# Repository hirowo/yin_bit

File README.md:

# yin:bit
micro:bit用の拡張モジュールです。micro:bitでフルカラーLED(WS2812B)をコントロールできます。

## 特長
従来からmicro:bitでフルカラーLEDを点灯させるモジュール等はありましたが、  micro:bitから出力される3.3VをフルカラーLEDの電源として使っているものや、電源を単3電池×3本を前提にしている物が多く、安定して光らせられるLEDの数は多くはありませんでした。

本モジュールは、本モジュールについているUSBコネクタから電源供給することで、  micro:bitに給電しつつフルカラーLEDを5V給電することが可能で、micro:bitからフルカラーLEDに給電する際より多くの数のLEDを安定して光らせることができます。

フルカラーLEDの点灯を一時的に抑えたいとき等のために、フルカラーLEDの電源ON/OFFスイッチも実装してあります。

Groveコネクタも実装してありますので、センサの値に応じて好きな色に光らせるといったこともできます。

## 説明動画

## Ver2.0の特徴
光らせたいけどはんだ付けは敷居が高い…という声があり、フルカラーLED部分がGrove互換コネクタが付き、はんだ付け無しでyin:bitを扱えるようになりました。

下記のようなGrove互換コネクタ付きフルカラーLEDを使えます。
 - [Grove - RGB LED (WS2813 Mini)](https://www.seeedstudio.com/Grove-RGB-LED-WS2813-Mini-p-4269.html)
 - [Grove - RGB LED Ring (24-WS2813 Mini)](https://www.seeedstudio.com/Grove-RGB-LED-Ring-24-WS2813-Mini-p-4202.html)
 - [Grove - RGB LED Stick (20-WS2813 Mini)](https://www.seeedstudio.com/Grove-RGB-LED-Stick-20-WS2813-Mini-p-4271.html)
 - [HEX RGB LED Board (SK6812)](https://m5stack.com/products/hex-rgb-led-board-sk6812)
 - [SK6812 RGB LED Flex-strip](https://m5stack.com/collections/m5-unit/products/sk6812-rgb-led-flex-strip)

またいろんなものに組み込むための固定用ネジ穴が追加されました。固定用ネジ穴部を分離するとyin:bitと同サイズになります。

## 使い方

1. yin:bitをmicro:bitにネジで固定します。

2. micro:bitにUSBケーブルを接続します。(プログラムをアプリから無線で書き込む際は不要)

3. micro:bitにプログラムを書き込みます。(プログラムの例は[サンプル](#サンプル)参照)

4. yin:bitにUSBケーブルを差し込み電源と接続します。

5. yin:bitのLED電源スイッチをONします。

## スペック
 - サイズ(v1) : 50.8 × 22.0 × 6.5mm  
 - サイズ(v2) : 68.8 × 24.8 × 8.0mm
 - フルカラーLED用電源電圧(v2だとフルカラーLED用Grove互換コネクタ電源電圧) : 5V
 - フルカラーLED用電源最大電流値 : 2A
 - 入出力用Grove互換コネクタ電源電圧：3.3 V

## ピン
 - フルカラーLEDシリアルピン(v2だとフルカラーLED用Grove互換コネクタ) : P0 
 - 入出力用Grove互換コネクタ : P1/P2

## どこで買える？
 - [スイッチサイエンス](https://www.switch-science.com/catalog/5431/)
 - [スイッチサイエンス(コネクタ実装版)](https://www.switch-science.com/catalog/5821/)
 - [マルツオンライン](https://www.marutsu.co.jp/pc/i/1559574/)
 - [シリコンハウス共立](http://blog.siliconhouse.jp/archives/52170700.html)
 - [Shigezone](https://twitter.com/ShigezoneAkiba/status/1170178701419405312)
 
## サンプル

20個のLEDをついたフルカラーLEDテープを使うことを想定します。

micro:bitでフルカラーLEDを使う場合は「拡張機能」の「NeoPixel」をプロジェクトに追加してください。

### LEDを全て赤色に光らせる

[プログラム例](https://makecode.microbit.org/_FkpHuT0tiH0w)

### LEDを虹色に光らせて流す

[プログラム例](https://makecode.microbit.org/_2kAJboFzL6Ek)

### [Groveのジョイスティック](http://wiki.seeedstudio.com/Grove-Thumb_Joystick/)を使って操作する

[プログラム例](https://makecode.microbit.org/_hW461R9WmUEq)

### 無線を使って遠隔で電飾を操作する

[プログラム例](https://makecode.microbit.org/_WzrJAp9o9Hsq)

### [Groveの超音波距離センサ](http://wiki.seeedstudio.com/Grove-Ultrasonic_Ranger/)を使って操作する

[プログラム例](https://makecode.microbit.org/_3hC7kxe1rCEK)

### おまけ:サーボモーターを動かす

サーボモーターにも使えます。サーボモーターのコードとyin:bitを下記のように繋いでください。

|サーボモーター|yin:bit|
|:-----------:|:------------:|
|茶色|GND|
|赤色|5V|
|黄色|LED_P0|

[プログラム例](https://makecode.microbit.org/_HUk0EjgW45yJ)

## 作品例

### [電飾エプロン](https://twitter.com/GomiHgy/status/1124863205099036674)(by[五味](https://twitter.com/GomiHgy))

### [micro:bitで光るスカート作ったで](https://www.nicovideo.jp/watch/sm35141886)(by[ましぐれ](https://twitter.com/mashigure))

### [サイバリアン電飾](https://twitter.com/i/moments/1194228358986383362)(by[RealizePlus](https://twitter.com/Realize_Plus))

### [光るウエディングドレスと連動する電飾キャンドルサービスを作ってみた](https://youtu.be/PWPQaGGIQgU)(by[静丘](https://twitter.com/Siz_oka))

## 終わりに

yin:bitの改良点がありましたら、ぜひIsuuesに書いてください。
こんな作品作ったよ！という方は [#yinbit](https://twitter.com/search?q=%23yinbit&src=typed_query) を付けてSNSなどで公開してくださると嬉しいです。
よい電飾ライフを！

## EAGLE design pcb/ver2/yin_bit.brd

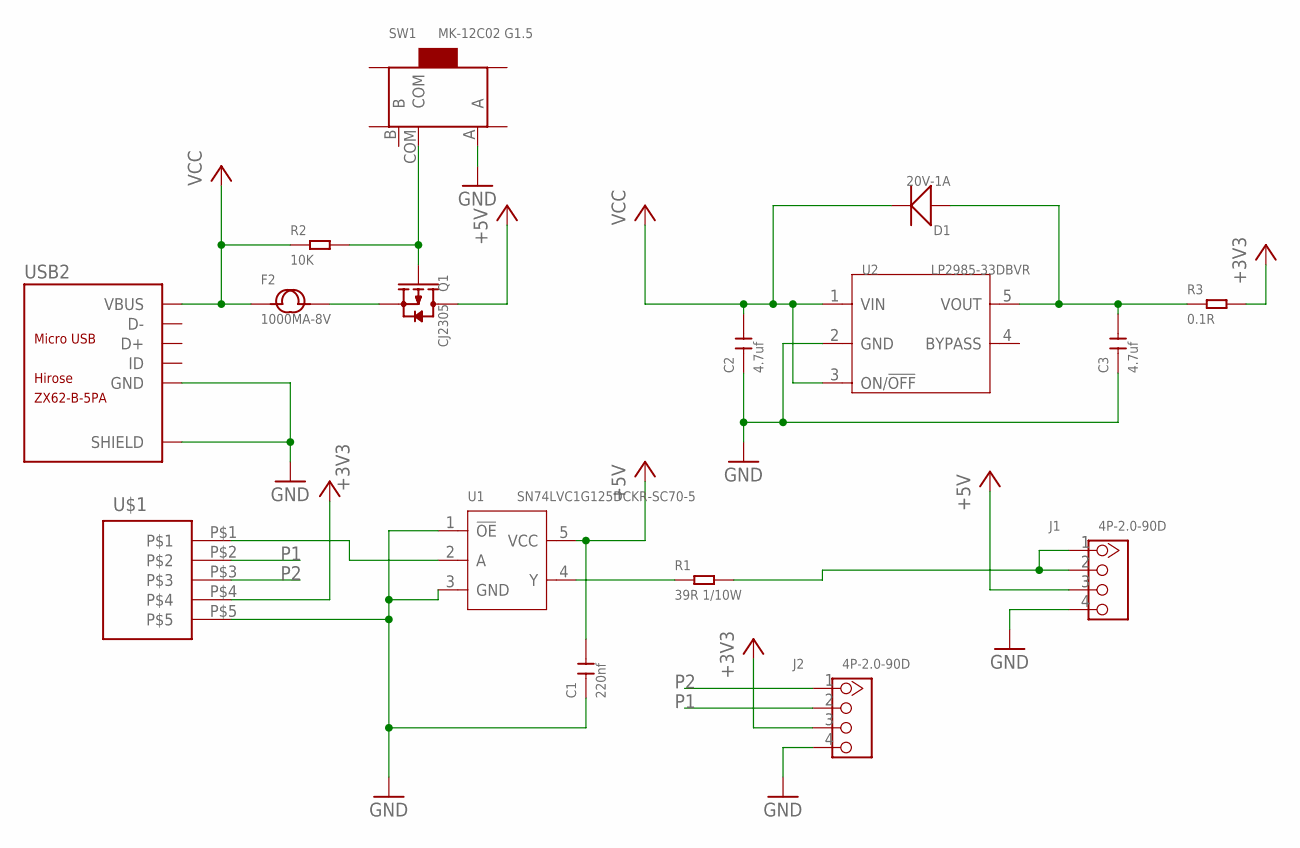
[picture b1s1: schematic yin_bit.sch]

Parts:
C1: 220nf; C0603
C2, C3: 4.7uf; C0603
D1: 20V-1A; SOD-123
F2: 1000MA-8V; F1206
J1, J2: 4P-2.0-90D; HW4-2.0-90D
Q1: CJ2305; SOT-23
R1: 39R 1/10W; R0603
R2: 10K; R0603
R3: 0.1R; R0805
SW1: MK-12C02 G1.5; SW7-SMD-L6.7X2.7X3.2MM
U1: SN74LVC1G125DCKR-SC70-5; SC-70-5
U2: LP2985-33DBVR; SOT-23-5
U$1: MICROBIT-HOLL
USB2: ZX62-B-5PA; MICRO-USB5+6P-SMD-0.65-AB

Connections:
+3V3: J2.3, R3.2, U$1.P$4
+5V: C1.2, J1.3, Q1.3 (D), U1.5 (VCC)
GND: C1.1, C2.1, C3.1, J1.4, J2.4, SW1.A, U1.1 (!OE!), U1.3 (GND), U2.2 (GND), U$1.P$5, USB2.5 (GND), USB2.P1 (SHIELD), USB2.P2 (SHIELD), USB2.P3 (SHIELD), USB2.P4 (SHIELD), USB2.P5 (SHIELD), USB2.P6 (SHIELD)
unnamed: U1.2 (A), U$1.P$1
unnamed: R1.1, U1.4 (Y)
unnamed: J1.1, J1.2, R1.2
unnamed: Q1.1 (G), R2.2, SW1.COM
unnamed: F2.2, Q1.2 (S)
unnamed: C3.2, D1.+, R3.1, U2.5 (VOUT)
P1: J2.2, U$1.P$2
P2: J2.1, U$1.P$3
VCC: C2.2, D1.-, F2.1, R2.1, U2.1 (VIN), U2.3 (ON/!OFF), USB2.1 (VBUS)

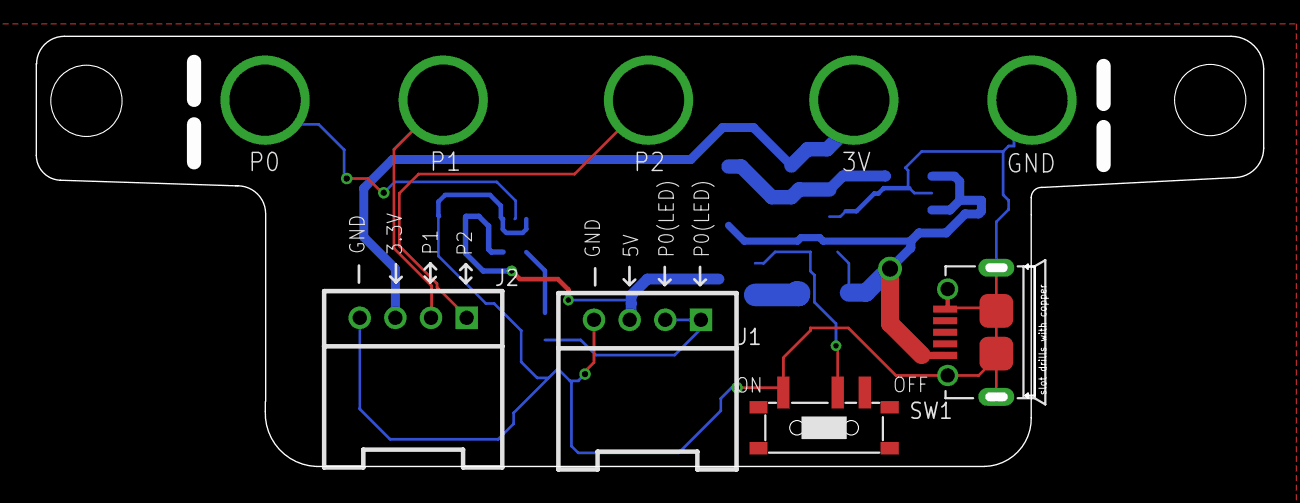
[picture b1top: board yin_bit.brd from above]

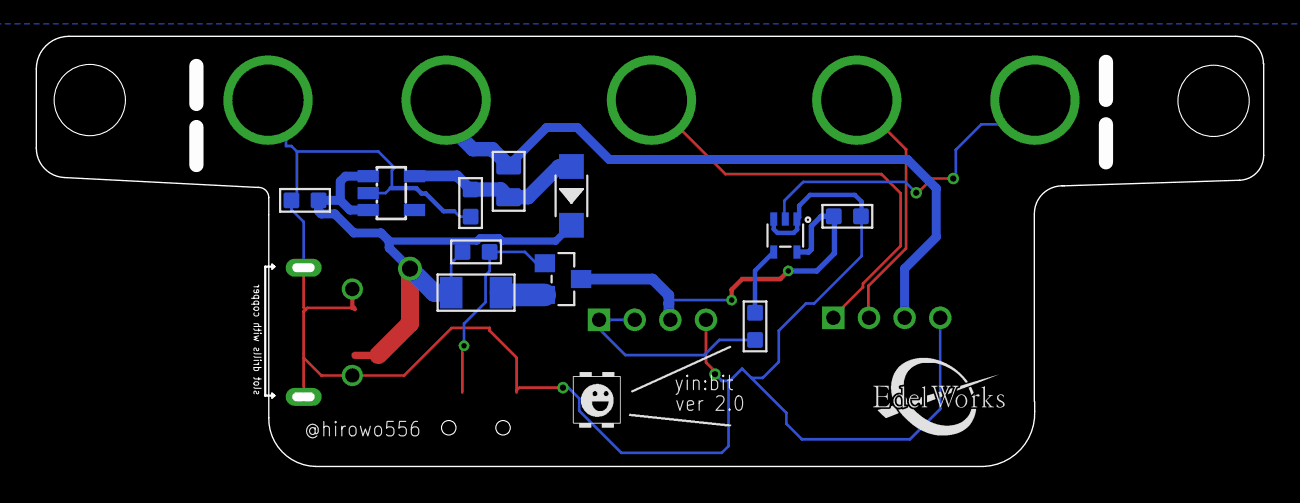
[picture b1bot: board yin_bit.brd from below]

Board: 2 copper layers, 68.2 x 23.4 mm, 16 parts (11 on the bottom side), 12 nets.

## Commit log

2019-01-18 Readmeの説明を追加
2019-01-18 回路データをアップデート
2019-03-12 READMEの説明を更新
2019-03-12 GIF動画が表示されない問題の改善
2019-03-12 GIF動画を軽量化
2019-03-12 使い方説明用画像を追加
2019-03-12 README.md使い方の説明に画像を追加
2019-04-13 基板サイズ修正
    基板サイズを修正、USBの干渉問題
2019-04-21 サーボモーターの動作例の追加
2019-05-22 使っていただいた作品を追加
    「micro:bitで光るスカート作ったで」を追加
2019-11-12 サイバリアン電飾を追加
2019-11-12 サイバリアン電飾の画像にリンク追加
2019-12-05 電飾エプロンを作品例に追加
2019-12-05 フルカラーLED用電源最大電流値の記述を追加
2019-12-06 距離センサデモ動画の追加
2019-12-06 Groveの超音波距離センサを使って操作するを追加及び説明微調整
2020-01-10 クリスマスツリーをつくろうを追加
2020-02-19 どこで買える？を追加
2020-07-02 基板関連データをPCBディレクトリに移動
2020-07-07 ver2に回路データをアップ
    ver2に回路データをアップ
2020-07-08 ver2.0用画像ファイルを追加
2020-07-08 v2.0の説明を追加
2020-07-08 #yinbitのリンクを追加
2020-07-08 レイアウト修正
2020-09-29 光るウエディングドレスと連動する電飾キャンドルサービスを作ってみたを追加
2021-02-22 説明動画を追加
